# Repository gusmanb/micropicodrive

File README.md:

# MicroPicoDrive - An internal replacement of the Sinclair QL Microdrive.

## UPDATE 22/03/2023

The device has been tested and patched to work with Minerva. Yup!
Also, the PCB has been modified, it should now be correctly placed but I'm waiting to receive a new batch of PCB's, until then I can't ensure 100% that it is totally fixed.

The Wiki has been set in place with documentation on how to assemble and use the device.

The BOM has been added to the Hardware folder and contains links to the more uncommon components.

Have fun!

# Initial commit

WARNING! This is a work in progress, I need to test it with Minerva ROM and do some adjustments to the PCB, be ware!

So, I got a Sinclair QL some months ago, I wanted one for many many years, I'm a Sinclair fan and I always have been in the Spectrum world and the QL always has been something that I wanted to get.
The unit I got was a broken one, it was stored since the 80's in a repair shop, when I got it the machine was non-working, without microdrives, with a faulty membrane and without a single screw, so the first that I did was to repair it.

And once I got it fully working I wanted to load something, but without microdrives it was a bit difficult... xD

I checked which solutions were available but I didn't liked none so I decided to create my own replacement, armed with my [logic analizer](https://github.com/gusmanb/logicanalyzer) and patience I learnt the internals of the microdrive protocol and created an internal replacement that uses "cartridges" and can be installed in the internal space of the QL.

And this is what I got:

The device is based in an RP2040 (I love the PIO units, those damn things are a wonder!) and some level shifters... and that's it. Well, that's it for the internal unit, there is also a screen, some buttons and an SD card holder for the cartridge!

The thing is completelly working with the stock rom, it can load programs without problems, can format cartridges, store images, etc, all without problems.

Also, I found that a lot of the software is stored as Zip files, the device right now supports MDV, IMG and my own custom format, so I checked the available utilities to manipulate MDV images and... it was a boomer to find that there is no updated one, only mdvtools that is ancient and after compiling manually it I found that most of the converted images were flawed.

So, again, I decided to create mi own solution, and this is what I finally got:

It can create MDV images from the ground, import MDV and ZIP files (and yes, it supports the QL zip format, it preserves the executable and data space attributes), manipulate the existing files, extract them, etc, so with this finally I got a full toolset for the QL!

Now I'm waiting for the components to build a 512Kb RAM expansion and from there I don't know where I will continue, may be a floppy drive emulator? IDE interface? Not sure, but the first is to add those 512Kb and a Minerva ROM to test the microdrive.

In any case, this is a work in progress, beware that I need to do some adjustments to the PCB and finish some tools for the software.

If you want more info don't esitate to contact me.

Have fun!

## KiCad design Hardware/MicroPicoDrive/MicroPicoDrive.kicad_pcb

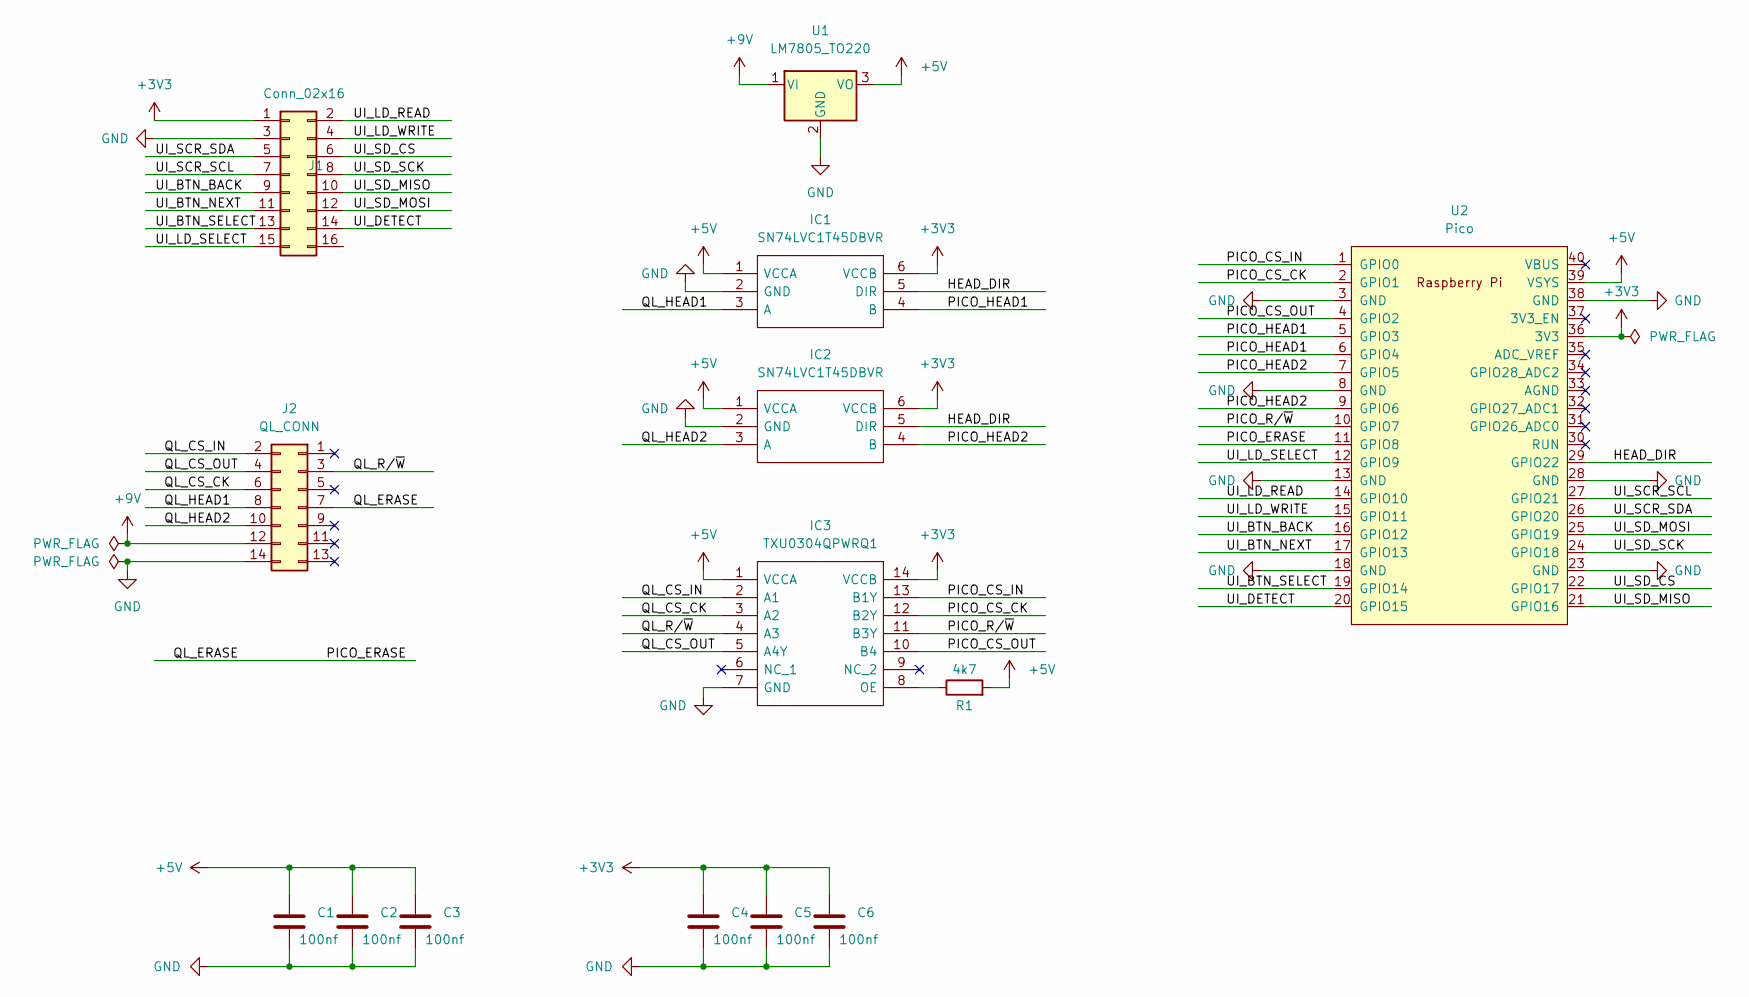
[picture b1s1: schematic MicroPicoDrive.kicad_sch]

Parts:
C1, C2, C3, C4, C5, C6: 100nf; C_0603_1608Metric
IC1, IC2: SN74LVC1T45DBVR; SOT95P280X145-6N; Mouser Part Number 595-SN74LVC1T45DBVR
IC3: TXU0304QPWRQ1; Mouser Part Number 595-TXU0304QPWRQ1
J1: Conn_02x16; Edge_connector_02x08
J2: QL_CONN; PinHeader_2x07_P2.54mm_Vertical
R1: 4k7; R_0603_1608Metric
U1: LM7805_TO220; TO-220-3_Vertical
U2: Pico; RPi_Pico_SMD_TH

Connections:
+3V3: C4.1, C5.1, C6.1, IC1.6 (VCCB), IC2.6 (VCCB), IC3.14 (VCCB), J1.1, U2.36 (3V3)
+5V: C1.1, C2.1, C3.1, IC1.1 (VCCA), IC2.1 (VCCA), IC3.1 (VCCA), R1.2, U1.3 (VO), U2.39 (VSYS)
+9V: J2.12, U1.1 (VI)
/HEAD_DIR: IC1.5 (DIR), IC2.5 (DIR), U2.29 (GPIO22)
/PICO_CS_CK: IC3.12 (B2Y), U2.2 (GPIO1)
/PICO_CS_IN: IC3.13 (B1Y), U2.1 (GPIO0)
/PICO_CS_OUT: IC3.10 (B4), U2.4 (GPIO2)
/PICO_ERASE: J2.7, U2.11 (GPIO8)
/PICO_HEAD1: IC1.4 (B), U2.5 (GPIO3), U2.6 (GPIO4)
/PICO_HEAD2: IC2.4 (B), U2.7 (GPIO5), U2.9 (GPIO6)
/PICO_R/~W: IC3.11 (B3Y), U2.10 (GPIO7)
/QL_CS_CK: IC3.3 (A2), J2.6
/QL_CS_IN: IC3.2 (A1), J2.2
/QL_CS_OUT: IC3.5 (A4Y), J2.4
/QL_HEAD1: IC1.3 (A), J2.8
/QL_HEAD2: IC2.3 (A), J2.10
/QL_R/~W: IC3.4 (A3), J2.3
/UI_BTN_BACK: J1.9, U2.16 (GPIO12)
/UI_BTN_NEXT: J1.11, U2.17 (GPIO13)
/UI_BTN_SELECT: J1.13, U2.19 (GPIO14)
/UI_DETECT: J1.14, U2.20 (GPIO15)
/UI_LD_READ: J1.2, U2.14 (GPIO10)
/UI_LD_SELECT: J1.15, U2.12 (GPIO9)
/UI_LD_WRITE: J1.4, U2.15 (GPIO11)
/UI_SCR_SCL: J1.7, U2.27 (GPIO21)
/UI_SCR_SDA: J1.5, U2.26 (GPIO20)
/UI_SD_CS: J1.6, U2.22 (GPIO17)
/UI_SD_MISO: J1.10, U2.21 (GPIO16)
/UI_SD_MOSI: J1.12, U2.25 (GPIO19)
/UI_SD_SCK: J1.8, U2.24 (GPIO18)
GND: C1.2, C2.2, C3.2, C4.2, C5.2, C6.2, IC1.2 (GND), IC2.2 (GND), IC3.7 (GND), J1.3, J2.14, U1.2 (GND), U2.3 (GND), U2.8 (GND), U2.13 (GND), U2.18 (GND), U2.23 (GND), U2.28 (GND), U2.38 (GND)
unnamed: IC3.8 (OE), R1.1

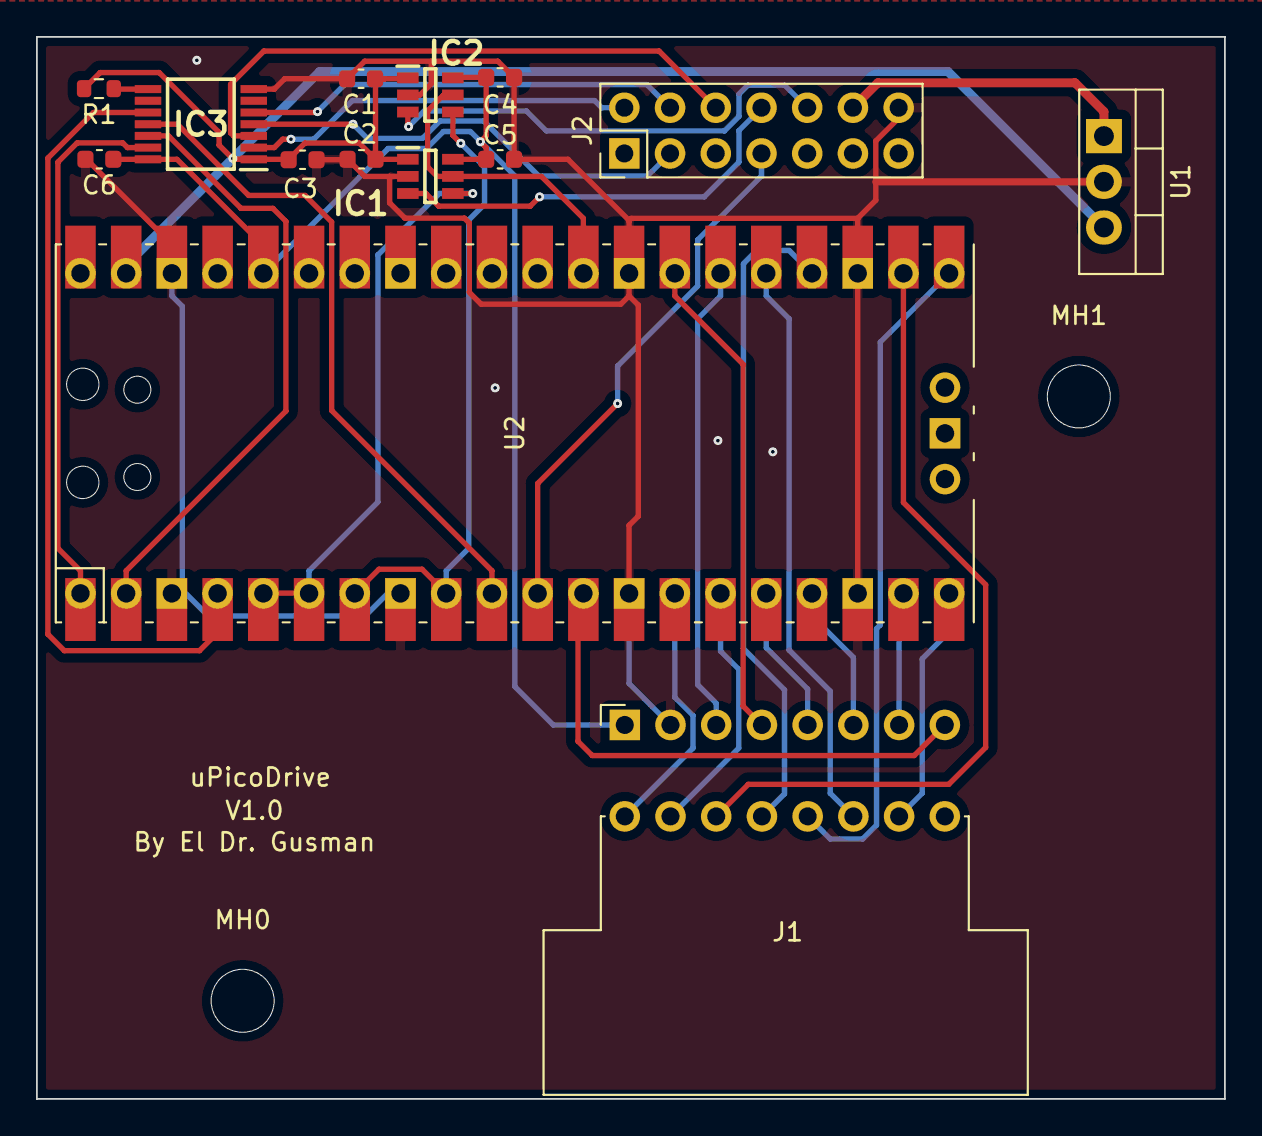
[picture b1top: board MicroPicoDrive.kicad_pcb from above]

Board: 2 copper layers, 66.0 x 59.0 mm, 16 parts (0 on the bottom side), 32 nets.

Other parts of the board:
MH0, MH1: MountingHole_3.5mm

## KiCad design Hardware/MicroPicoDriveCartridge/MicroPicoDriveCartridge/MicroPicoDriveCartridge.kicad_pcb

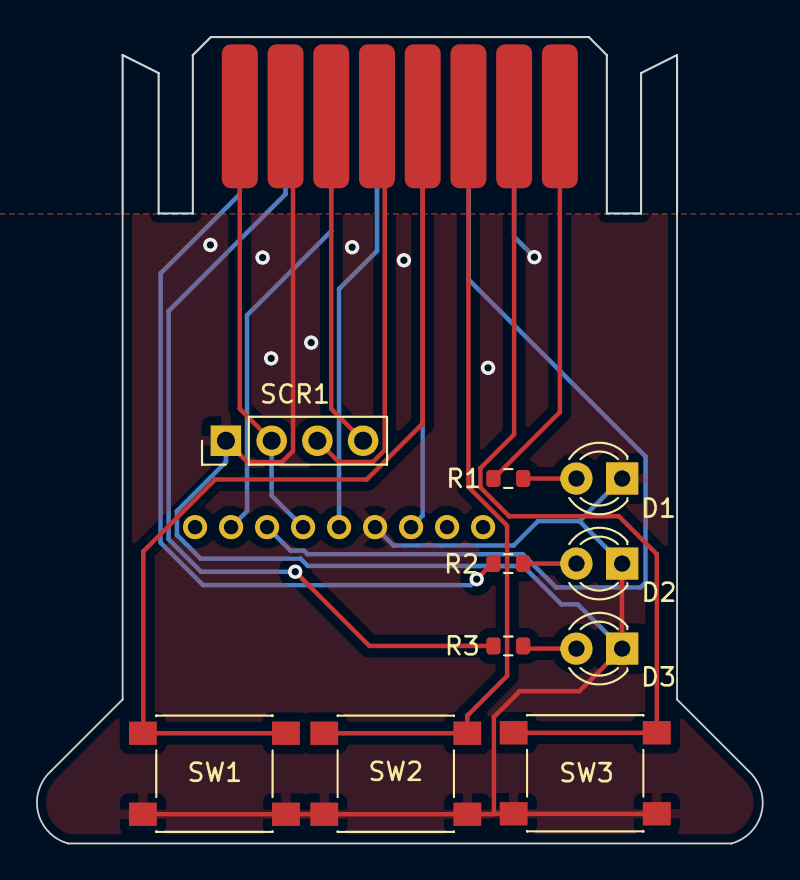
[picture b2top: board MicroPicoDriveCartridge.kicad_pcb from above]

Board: 2 copper layers, 40.3 x 44.8 mm, 12 parts (1 on the bottom side), 17 nets.

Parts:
D1, D2, D3: LED; LED_D3.0mm
J1: Conn_02x08_Odd_Even; Edge
R1, R2, R3: 1K; R_0603_1608Metric
SCR1: Screen
SD1: SDCard
SW1, SW2, SW3: SW_Push; SW_Push_1P1T_NO_6x6mm_H9.5mm

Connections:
+3V3: J1.1, SCR1.2 (VCC), SD1.6 (VCC)
/UI_BTN_BACK: J1.9, SW1.1
/UI_BTN_NEXT: J1.11, SW2.1
/UI_BTN_SELECT: J1.13, SW3.1
/UI_LD_READ: J1.2, R2.1
/UI_LD_SELECT: J1.15, R1.1
/UI_LD_WRITE: J1.4, R3.1
/UI_SCR_SCL: J1.7, SCR1.3 (SCL)
/UI_SCR_SDA: J1.5, SCR1.4 (SDA)
/UI_SD_CS: J1.6, SD1.8 (D3/CS)
/UI_SD_MISO: J1.10, SD1.3 (D0/MISO)
/UI_SD_MOSI: J1.12, SD1.7 (CMD/MOSI)
/UI_SD_SCK: J1.8, SD1.5 (CLK)
GND: D1.1 (K), D2.1 (K), D3.1 (K), J1.3, J1.14, SCR1.1 (GND), SD1.4 (GND), SW1.2, SW2.2, SW3.2
unnamed: D1.2 (A), R1.2
unnamed: D2.2 (A), R2.2
unnamed: D3.2 (A), R3.2

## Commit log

2023-09-19 Create LICENSE
2023-09-22 Updated PCB, added BOM and links, updated MDToolsUI
2023-09-22 Removed fabrication outputs from KiCad projects
2023-10-01 Corrected bug in mdvtools
2023-10-01 Removed executable outputs
2023-11-05 Updated PCBs
2024-04-27 Corrected MicroDriveCartridge missing constructor
2024-05-01 Updated libraries Changed publish profile
2024-07-12 Update MicroDriveControl.c
    Corrected DMA cancellation in drive deselection
